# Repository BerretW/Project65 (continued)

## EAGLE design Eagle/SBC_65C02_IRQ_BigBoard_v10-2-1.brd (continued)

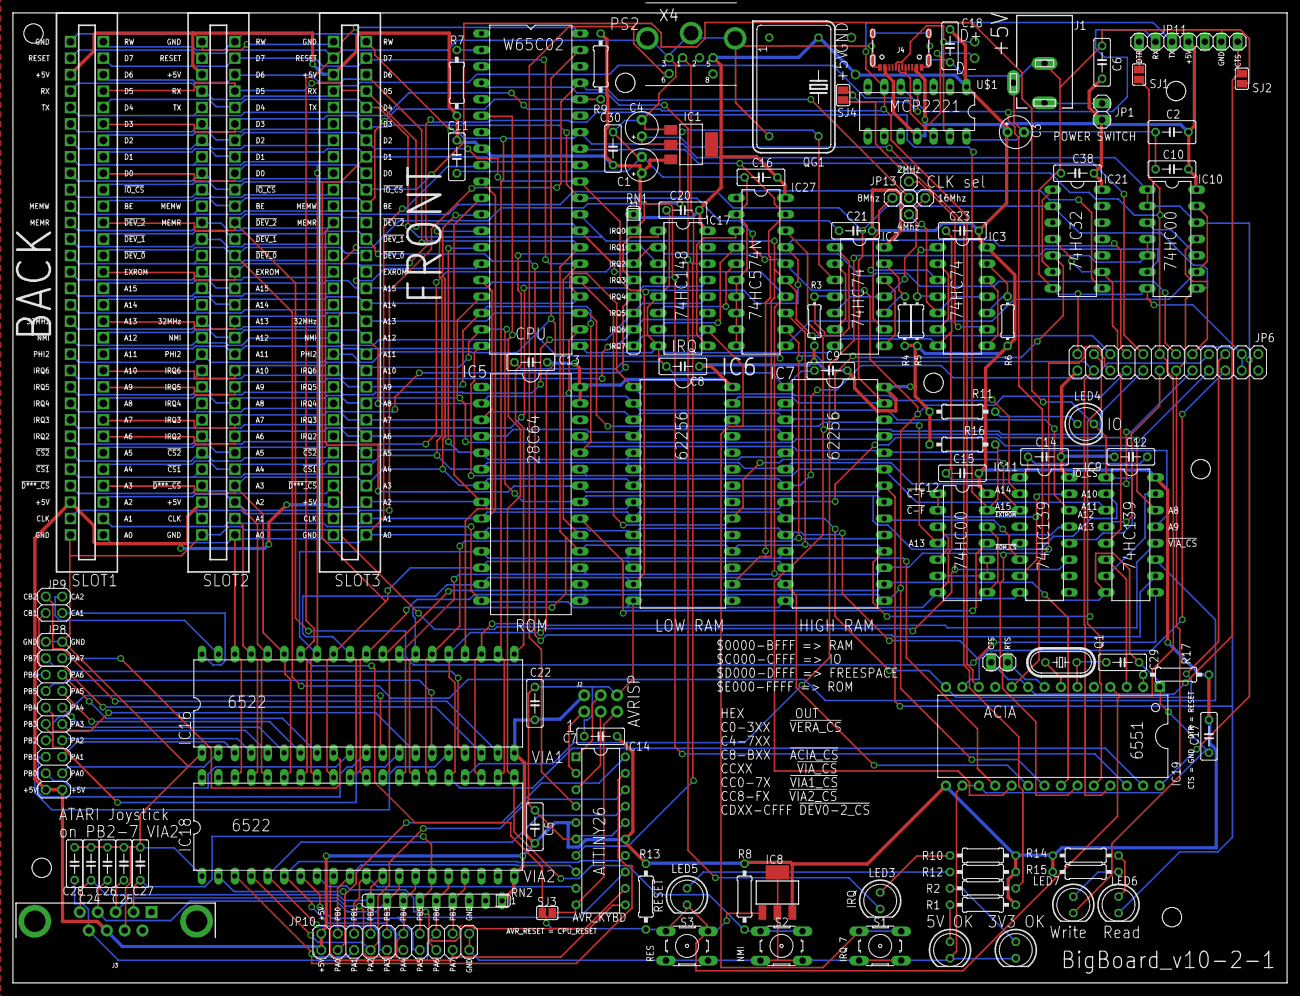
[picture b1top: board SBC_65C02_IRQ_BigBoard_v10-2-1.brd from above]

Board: 2 copper layers, 196.8 x 149.9 mm, 105 parts (0 on the bottom side), 155 nets.

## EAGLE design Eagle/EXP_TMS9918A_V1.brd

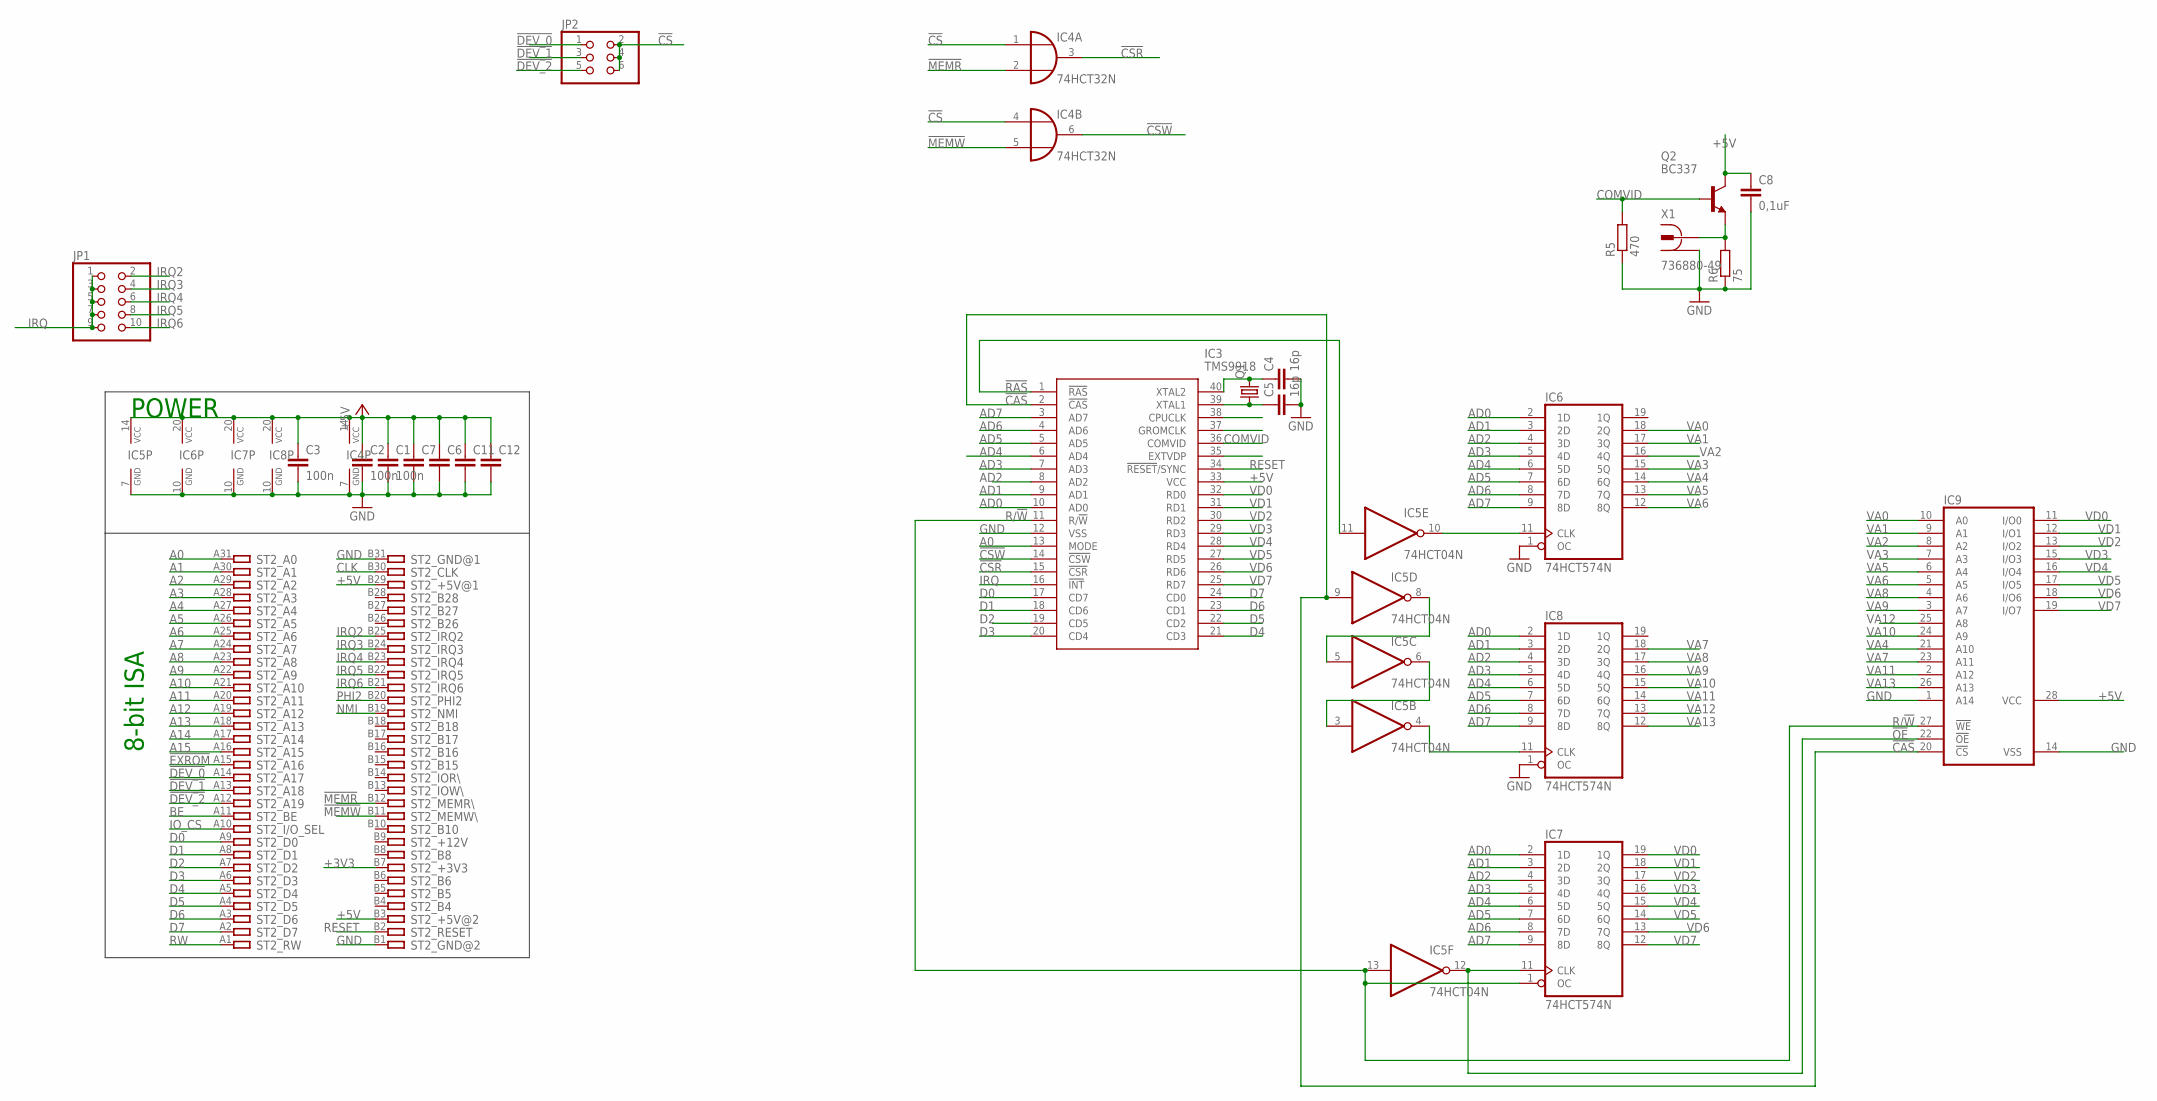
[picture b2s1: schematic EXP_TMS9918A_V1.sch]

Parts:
C1, C2, C3: 100n; C050-025X075
C4, C5: 16p; C050-024X044
C6, C7, C11, C12: C-EU050-035X075; C050-035X075
C8: 0,1uF; C050-024X044
IC3: TMS9918; DIP1524W53P254L5310H508Q40N
IC4: 74HCT32N; DIL14
IC5: 74HCT04N; DIL14
IC6, IC7, IC8: 74HCT574N; DIL20
IC9: 62256P; DIL28-6
JP1: PINHD-2X5; 2X05
JP2: PINHD-2X3; 2X03
Q1: CRYSTALHC49S; HC49/S
Q2: BC337; TO92
R5: 470; 0207/7
R6: 75; 0207/7
ST2: IBM8BIT_ISASHORT; APP_2X32_SHORT
X1: 736880-49

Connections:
!CAS: IC3.2 (!CAS), IC5.9 (I), IC9.20 (!CS)
!CS: IC4.1 (I0), IC4.4 (I0), JP2.2, JP2.4, JP2.6
!CSR: IC3.15 (!CSR), IC4.3 (O)
!CSW: IC3.14 (!CSW), IC4.6 (O)
!DEV_0: JP2.1, ST2.A14
!DEV_1: JP2.3, ST2.A13
!DEV_2: JP2.5, ST2.A12
!EXROM: ST2.A15
!MEMR: IC4.2 (I1), ST2.B12
!MEMW: IC4.5 (I1), ST2.B11
!OE: IC5.12 (O), IC7.11 (CLK), IC9.22 (!OE)
!RAS: IC3.1 (!RAS), IC5.11 (I)
+3V3: ST2.B7
+5V: C1.1, C2.1, C3.1, C6.1, C7.1, C8.1, C11.1, C12.1, IC3.33 (VCC), IC4.14 (VCC), IC5.14 (VCC), IC6.20 (VCC), IC7.20 (VCC), IC8.20 (VCC), IC9.28 (VCC), Q2.3 (C), ST2.B3, ST2.B29
A0: IC3.13 (MODE), ST2.A31
A1: ST2.A30
A2: ST2.A29
A3: ST2.A28
A4: ST2.A27
A5: ST2.A26
A6: ST2.A25
A7: ST2.A24
A8: ST2.A23
A9: ST2.A22
A10: ST2.A21
A11: ST2.A20
A12: ST2.A19
A13: ST2.A18
A14: ST2.A17
A15: ST2.A16
AD0: IC3.10 (AD0), IC6.2 (1D), IC7.2 (1D), IC8.2 (1D)
AD1: IC3.9 (AD1), IC6.3 (2D), IC7.3 (2D), IC8.3 (2D)
AD2: IC3.8 (AD2), IC6.4 (3D), IC7.4 (3D), IC8.4 (3D)
AD3: IC3.7 (AD3), IC6.5 (4D), IC7.5 (4D), IC8.5 (4D)
AD4: IC3.6 (AD4), IC6.6 (5D), IC7.6 (5D), IC8.6 (5D)
AD5: IC3.5 (AD5), IC6.7 (6D), IC7.7 (6D), IC8.7 (6D)
AD6: IC3.4 (AD6), IC6.8 (7D), IC7.8 (7D), IC8.8 (7D)
AD7: IC3.3 (AD7), IC6.9 (8D), IC7.9 (8D), IC8.9 (8D)
BE: ST2.A11
CLK: ST2.B30
COMVID: IC3.36 (COMVID), Q2.2 (B), R5.2
D0: IC3.17 (CD7), ST2.A9
D1: IC3.18 (CD6), ST2.A8
D2: IC3.19 (CD5), ST2.A7
D3: IC3.20 (CD4), ST2.A6
D4: IC3.21 (CD3), ST2.A5
D5: IC3.22 (CD2), ST2.A4
D6: IC3.23 (CD1), ST2.A3
D7: IC3.24 (CD0), ST2.A2
GND: C1.2, C2.2, C3.2, C4.2, C5.2, C6.2, C7.2, C8.2, C11.2, C12.2, IC3.12 (VSS), IC4.7 (GND), IC5.7 (GND), IC6.1 (OC), IC6.10 (GND), IC7.10 (GND), IC8.1 (OC), IC8.10 (GND), IC9.1 (A14), IC9.14 (VSS), R5.1, R6.1, ST2.B1, ST2.B31, X1.1, X1.1@1 (1), X1.1@2 (1)
IO_CS: ST2.A10
IRQ: IC3.16 (!INT), JP1.1, JP1.3, JP1.5, JP1.7, JP1.9
IRQ2: JP1.2, ST2.B25
IRQ3: JP1.4, ST2.B24
IRQ4: JP1.6, ST2.B23
IRQ5: JP1.8, ST2.B22
IRQ6: JP1.10, ST2.B21
unnamed: Q2.1 (E), R6.2, X1.2
unnamed: IC5.10 (O), IC6.11 (CLK)
unnamed: IC5.5 (I), IC5.8 (O)
unnamed: IC5.3 (I), IC5.6 (O)
unnamed: IC5.4 (O), IC8.11 (CLK)
unnamed: C4.1, IC3.40 (XTAL2), Q1.2
unnamed: C5.1, IC3.39 (XTAL1), Q1.1
NMI: ST2.B19
PHI2: ST2.B20
R/!W: IC3.11 (R/!W), IC5.13 (I), IC7.1 (OC), IC9.27 (!WE)
RESET: IC3.34 (!RESET!/SYNC), ST2.B2
RW: ST2.A1
VA0: IC6.18 (2Q), IC9.10 (A0)
VA1: IC6.17 (3Q), IC9.9 (A1)
VA2: IC6.16 (4Q), IC9.8 (A2)
VA3: IC6.15 (5Q), IC9.7 (A3)
VA4: IC6.14 (6Q), IC9.21 (A10)
VA5: IC6.13 (7Q), IC9.6 (A4)
VA6: IC6.12 (8Q), IC9.5 (A5)
VA7: IC8.18 (2Q), IC9.23 (A11)
VA8: IC8.17 (3Q), IC9.4 (A6)
VA9: IC8.16 (4Q), IC9.3 (A7)
VA10: IC8.15 (5Q), IC9.24 (A9)
VA11: IC8.14 (6Q), IC9.2 (A12)
VA12: IC8.13 (7Q), IC9.25 (A8)
VA13: IC8.12 (8Q), IC9.26 (A13)
VD0: IC3.32 (RD0), IC7.19 (1Q), IC9.11 (I/O0)
VD1: IC3.31 (RD1), IC7.18 (2Q), IC9.12 (I/O1)
VD2: IC3.30 (RD2), IC7.17 (3Q), IC9.13 (I/O2)
VD3: IC3.29 (RD3), IC7.16 (4Q), IC9.15 (I/O3)
VD4: IC3.28 (RD4), IC7.15 (5Q), IC9.16 (I/O4)
VD5: IC3.27 (RD5), IC7.14 (6Q), IC9.17 (I/O5)
VD6: IC3.26 (RD6), IC7.13 (7Q), IC9.18 (I/O6)
VD7: IC3.25 (RD7), IC7.12 (8Q), IC9.19 (I/O7)

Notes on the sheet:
POWER
8-bit ISA

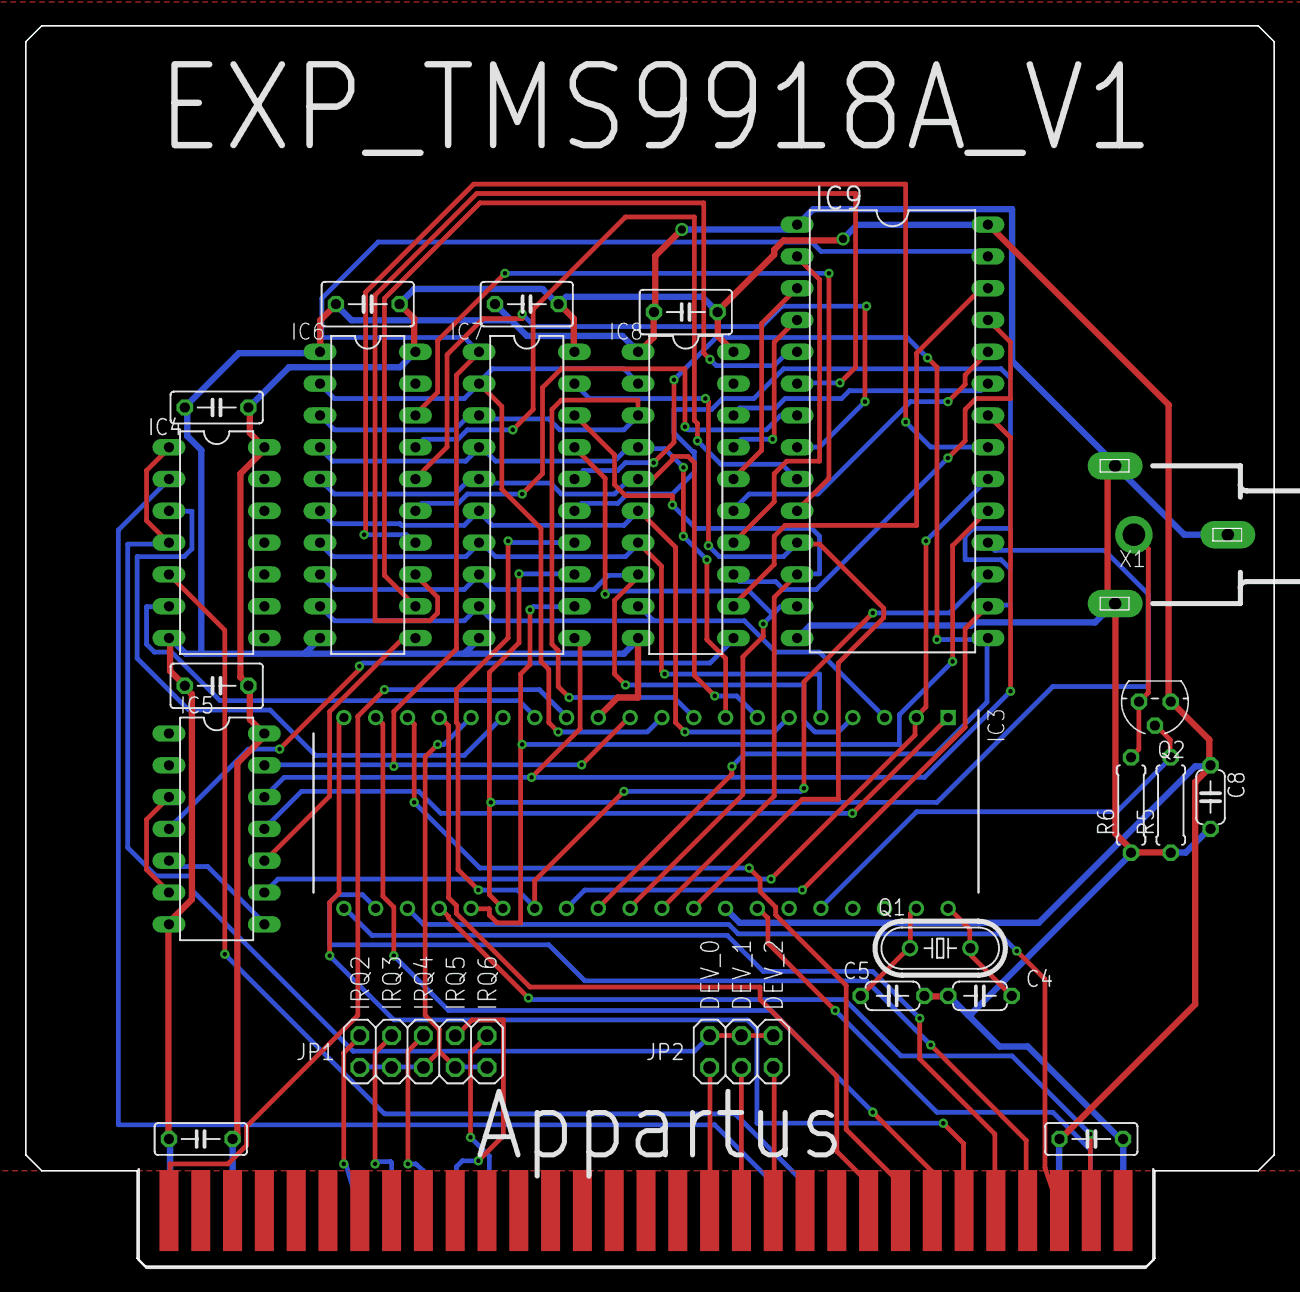
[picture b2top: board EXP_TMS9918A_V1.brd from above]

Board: 2 copper layers, 99.7 x 99.1 mm, 25 parts (0 on the bottom side), 68 nets.

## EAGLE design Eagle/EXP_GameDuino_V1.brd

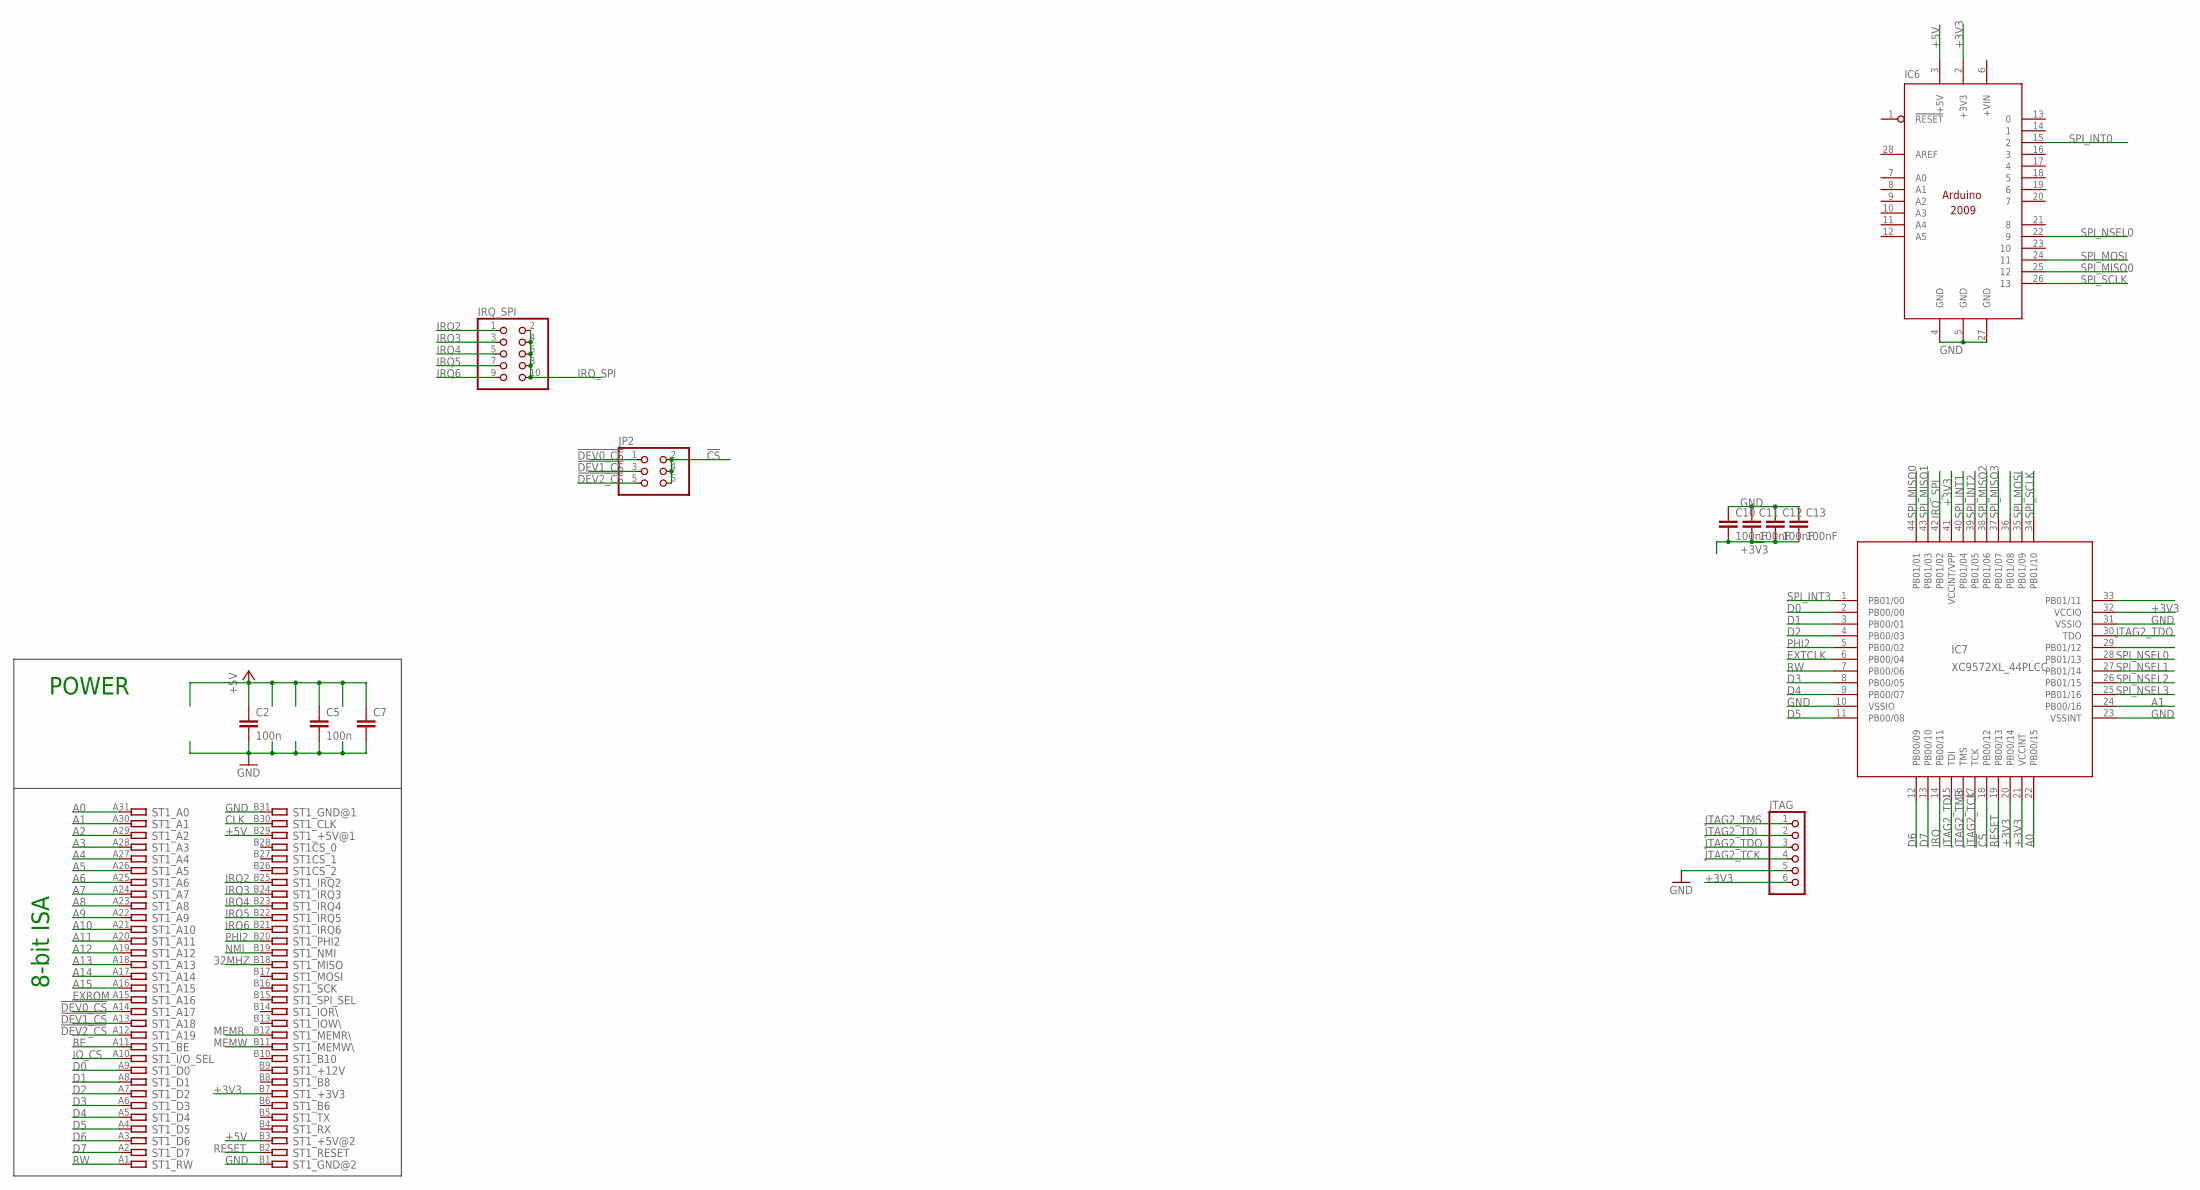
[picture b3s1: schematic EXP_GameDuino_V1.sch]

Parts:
C2, C5: 100n; C050-025X075
C7: C-EU050-035X075; C050-035X075
C10, C11, C12, C13: 100nF; C603
IC6: ARDUINO2009_10; ARDUINO2009
IC7: XC9572XL_44PLCC; S44
IRQ_SPI: PINHD-2X5; 2X05
JP2: PINHD-2X3; 2X03
JTAG: PINHD-1X6; 1X06
ST1: IBM8BIT_ISASHORT; APP_2X32_SHORT

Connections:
32MHZ: ST1.B18
!CS: IC7.18 (PB00/12), JP2.2, JP2.4, JP2.6
!DEV0_CS: JP2.1, ST1.A14
!DEV1_CS: JP2.3, ST1.A13
!DEV2_CS: JP2.5, ST1.A12
+3V3: C10.2, C11.2, C12.2, C13.2, IC6.2 (+3V3), IC7.20 (PB00/14), IC7.21 (VCCINT), IC7.32 (VCCIO), IC7.41 (VCCINT/VPP), JTAG.6, ST1.B7
+5V: C2.1, C5.1, C7.1, IC6.3 (+5V), ST1.B3, ST1.B29
A0: IC7.22 (PB00/15), ST1.A31
A1: IC7.24 (PB00/16), ST1.A30
A2: ST1.A29
A3: ST1.A28
A4: ST1.A27
A5: ST1.A26
A6: ST1.A25
A7: ST1.A24
A8: ST1.A23
A9: ST1.A22
A10: ST1.A21
A11: ST1.A20
A12: ST1.A19
A13: ST1.A18
A14: ST1.A17
A15: ST1.A16
BE: ST1.A11
CLK: ST1.B30
D0: IC7.2 (PB00/00), ST1.A9
D1: IC7.3 (PB00/01), ST1.A8
D2: IC7.4 (PB00/03), ST1.A7
D3: IC7.8 (PB00/05), ST1.A6
D4: IC7.9 (PB00/07), ST1.A5
D5: IC7.11 (PB00/08), ST1.A4
D6: IC7.12 (PB00/09), ST1.A3
D7: IC7.13 (PB00/10), ST1.A2
EXROM: ST1.A15
EXTCLK: IC7.6 (PB00/04)
GND: C2.2, C5.2, C7.2, C10.1, C11.1, C12.1, C13.1, IC6.4 (GND), IC6.5 (GND), IC6.27 (GND), IC7.10 (VSSIO), IC7.23 (VSSINT), IC7.31 (VSSIO), JTAG.5, ST1.B1, ST1.B31
IO_CS: ST1.A10
IRQ: IC7.14 (PB00/11)
IRQ2: IRQ_SPI.1, ST1.B25
IRQ3: IRQ_SPI.3, ST1.B24
IRQ4: IRQ_SPI.5, ST1.B23
IRQ5: IRQ_SPI.7, ST1.B22
IRQ6: IRQ_SPI.9, ST1.B21
IRQ_SPI: IC7.42 (PB01/02), IRQ_SPI.2, IRQ_SPI.4, IRQ_SPI.6, IRQ_SPI.8, IRQ_SPI.10
JTAG2_TCK: IC7.17 (TCK), JTAG.4
JTAG2_TDI: IC7.15 (TDI), JTAG.2
JTAG2_TDO: IC7.30 (TDO), JTAG.3
JTAG2_TMS: IC7.16 (TMS), JTAG.1
MEMR: ST1.B12
MEMW: ST1.B11
NMI: ST1.B19
PHI2: IC7.5 (PB00/02), ST1.B20
RESET: IC7.19 (PB00/13), ST1.B2
RW: IC7.7 (PB00/06), ST1.A1
SPI_INT0: IC6.15 (2)
SPI_INT1: IC7.40 (PB01/04)
SPI_INT2: IC7.39 (PB01/05)
SPI_INT3: IC7.1 (PB01/00)
SPI_MISO0: IC6.25 (12), IC7.44 (PB01/01)
SPI_MISO1: IC7.43 (PB01/03)
SPI_MISO2: IC7.38 (PB01/06)
SPI_MISO3: IC7.37 (PB01/07)
SPI_MOSI: IC6.24 (11), IC7.35 (PB01/09)
SPI_NSEL0: IC6.22 (9), IC7.28 (PB01/13)
SPI_NSEL1: IC7.27 (PB01/14)
SPI_NSEL2: IC7.26 (PB01/15)
SPI_NSEL3: IC7.25 (PB01/16)
SPI_SCLK: IC6.26 (13), IC7.34 (PB01/10)

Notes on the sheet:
POWER
8-bit ISA

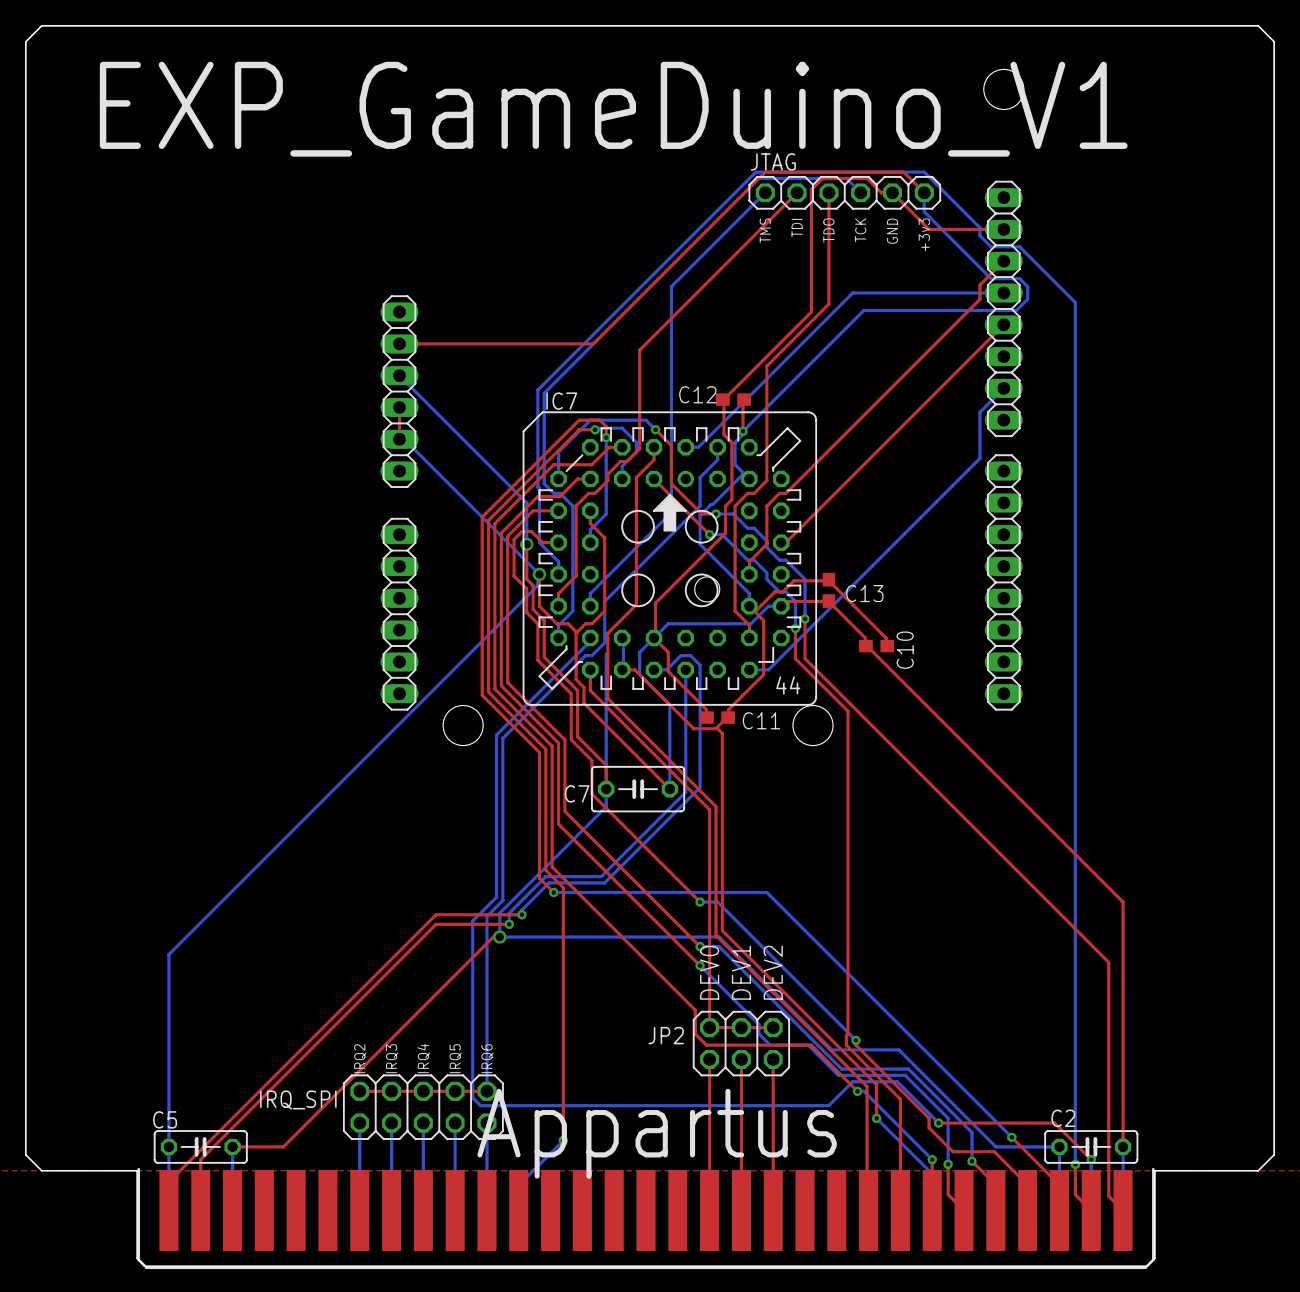
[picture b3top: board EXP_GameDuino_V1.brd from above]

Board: 2 copper layers, 99.7 x 99.1 mm, 13 parts (0 on the bottom side), 34 nets.

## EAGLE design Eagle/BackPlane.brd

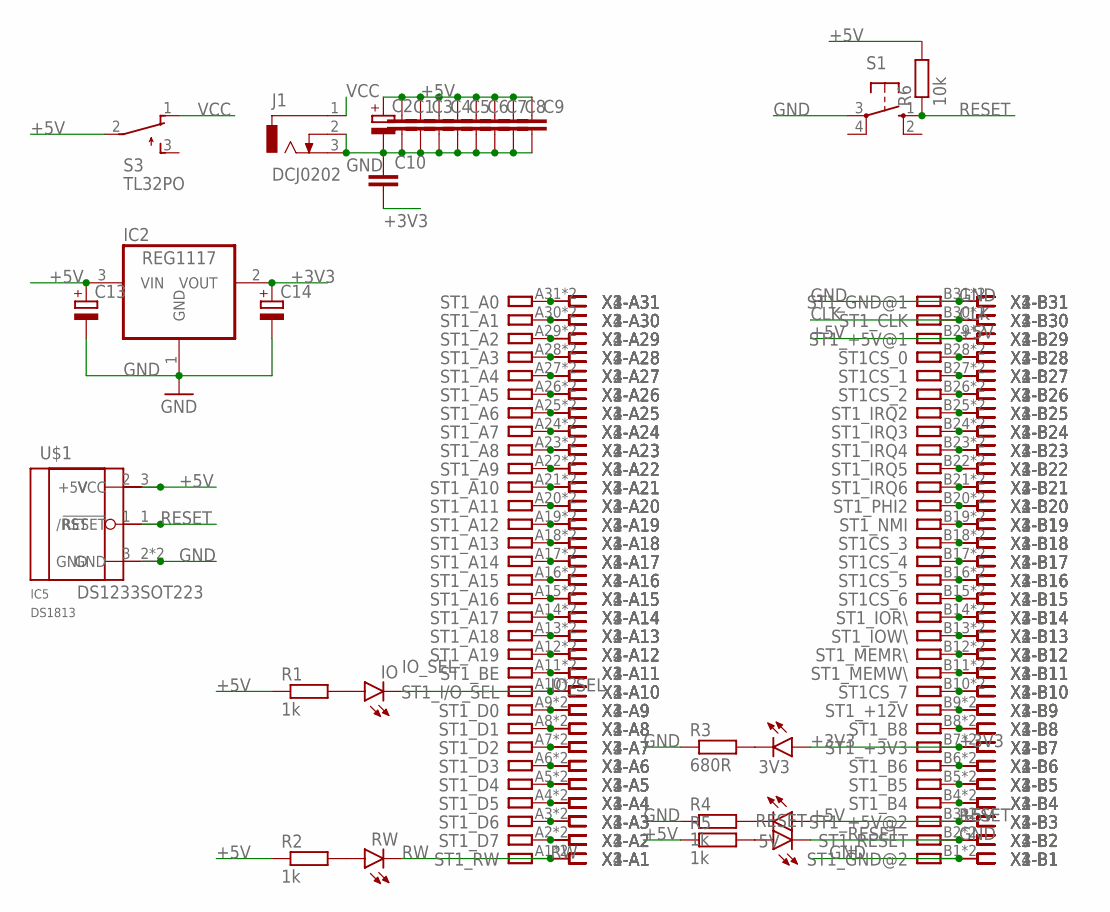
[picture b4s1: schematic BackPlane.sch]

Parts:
3V3, 5V: LED3MM
C1, C3, C4, C5, C6, C7, C8, C9: C-EU050-024X044; C050-024X044
C2: CPOL-EUE3.5-8; E3,5-8
C10: C-EU025-024X044; C025-024X044
C13, C14: CPOL-EUE2.5-5; E2,5-5
IC2: REG1117; SOT223
IC5: DS1813; TO-92
IO: LED3MM
J1: DCJ0202
R1, R2, R4, R5: 1k; 0207/7
R3: 680R; 0207/7
R6: 10k; 0207/7
RESET: LED3MM
RW: LED3MM
S1: 10-XX; B3F-10XX
S3: TL32PO; TL3XPO
ST1: IBM8BIT_ISA; APP_2X32_DOUBLE
U$1: DS1233SOT223; SOT223
X1, X2, X3, X4: ISA-SLOT; ISA-8

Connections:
+3V3: 3V3.A, C10.2, C14.+, IC2.2 (VOUT), ST1.B7, ST1.B38, X1.B7, X2.B7, X3.B7, X4.B7
+5V: 5V.A, C1.1, C2.+, C3.1, C4.1, C5.1, C6.1, C7.1, C8.1, C9.1, C13.+, IC2.3 (VIN), IC5.2 (+5V), R1.1, R2.1, R5.1, R6.2, S3.2, ST1.B3, ST1.B29, ST1.B34, ST1.B60, U$1.3 (VCC), X1.B3, X1.B29, X2.B3, X2.B29, X3.B3, X3.B29, X4.B3, X4.B29
CLK: ST1.B30, ST1.B61, X1.B30, X2.B30, X3.B30, X4.B30
GND: C1.2, C2.-, C3.2, C4.2, C5.2, C6.2, C7.2, C8.2, C9.2, C10.1, C13.-, C14.-, IC2.1 (GND), IC5.3 (GND), J1.2, J1.3, R3.1, R4.1, S1.3, ST1.B1, ST1.B31, ST1.B32, ST1.B62, U$1.2 (GND), U$1.4 (GND), X1.B1, X1.B31, X2.B1, X2.B31, X3.B1, X3.B31, X4.B1, X4.B31
IO_SEL: IO.K (C), ST1.A10, ST1.A41, X1.A10, X2.A10, X3.A10, X4.A10
unnamed: IO.A, R1.2
unnamed: ST1.A2, ST1.A33, X1.A2, X2.A2, X3.A2, X4.A2
unnamed: ST1.A3, ST1.A34, X1.A3, X2.A3, X3.A3, X4.A3
unnamed: ST1.A4, ST1.A35, X1.A4, X2.A4, X3.A4, X4.A4
unnamed: ST1.A5, ST1.A36, X1.A5, X2.A5, X3.A5, X4.A5
unnamed: ST1.A6, ST1.A37, X1.A6, X2.A6, X3.A6, X4.A6
unnamed: ST1.A7, ST1.A38, X1.A7, X2.A7, X3.A7, X4.A7
unnamed: ST1.A8, ST1.A39, X1.A8, X2.A8, X3.A8, X4.A8
unnamed: ST1.A9, ST1.A40, X1.A9, X2.A9, X3.A9, X4.A9
unnamed: R2.2, RW.A
unnamed: ST1.A11, ST1.A42, X1.A11, X2.A11, X3.A11, X4.A11
unnamed: ST1.A12, ST1.A43, X1.A12, X2.A12, X3.A12, X4.A12
unnamed: ST1.A13, ST1.A44, X1.A13, X2.A13, X3.A13, X4.A13
unnamed: ST1.A14, ST1.A45, X1.A14, X2.A14, X3.A14, X4.A14
unnamed: ST1.A15, ST1.A46, X1.A15, X2.A15, X3.A15, X4.A15
unnamed: ST1.A16, ST1.A47, X1.A16, X2.A16, X3.A16, X4.A16
unnamed: ST1.A17, ST1.A48, X1.A17, X2.A17, X3.A17, X4.A17
unnamed: ST1.A18, ST1.A49, X1.A18, X2.A18, X3.A18, X4.A18
unnamed: ST1.A19, ST1.A50, X1.A19, X2.A19, X3.A19, X4.A19
unnamed: ST1.A20, ST1.A51, X1.A20, X2.A20, X3.A20, X4.A20
unnamed: ST1.A21, ST1.A52, X1.A21, X2.A21, X3.A21, X4.A21
unnamed: ST1.A22, ST1.A53, X1.A22, X2.A22, X3.A22, X4.A22
unnamed: ST1.A23, ST1.A54, X1.A23, X2.A23, X3.A23, X4.A23
unnamed: ST1.A24, ST1.A55, X1.A24, X2.A24, X3.A24, X4.A24
unnamed: ST1.A25, ST1.A56, X1.A25, X2.A25, X3.A25, X4.A25
unnamed: ST1.A26, ST1.A57, X1.A26, X2.A26, X3.A26, X4.A26
unnamed: ST1.A27, ST1.A58, X1.A27, X2.A27, X3.A27, X4.A27
unnamed: ST1.A28, ST1.A59, X1.A28, X2.A28, X3.A28, X4.A28
unnamed: ST1.A29, ST1.A60, X1.A29, X2.A29, X3.A29, X4.A29
unnamed: ST1.A30, ST1.A61, X1.A30, X2.A30, X3.A30, X4.A30
unnamed: ST1.A31, ST1.A62, X1.A31, X2.A31, X3.A31, X4.A31
unnamed: ST1.B4, ST1.B35, X1.B4, X2.B4, X3.B4, X4.B4
unnamed: ST1.B5, ST1.B36, X1.B5, X2.B5, X3.B5, X4.B5
unnamed: ST1.B6, ST1.B37, X1.B6, X2.B6, X3.B6, X4.B6
unnamed: ST1.B8, ST1.B39, X1.B8, X2.B8, X3.B8, X4.B8
unnamed: ST1.B9, ST1.B40, X1.B9, X2.B9, X3.B9, X4.B9
unnamed: ST1.B10, ST1.B41, X1.B10, X2.B10, X3.B10, X4.B10
unnamed: ST1.B11, ST1.B42, X1.B11, X2.B11, X3.B11, X4.B11
unnamed: ST1.B12, ST1.B43, X1.B12, X2.B12, X3.B12, X4.B12
unnamed: ST1.B13, ST1.B44, X1.B13, X2.B13, X3.B13, X4.B13
unnamed: ST1.B14, ST1.B45, X1.B14, X2.B14, X3.B14, X4.B14
unnamed: ST1.B15, ST1.B46, X1.B15, X2.B15, X3.B15, X4.B15
unnamed: ST1.B16, ST1.B47, X1.B16, X2.B16, X3.B16, X4.B16
unnamed: ST1.B17, ST1.B48, X1.B17, X2.B17, X3.B17, X4.B17
unnamed: ST1.B18, ST1.B49, X1.B18, X2.B18, X3.B18, X4.B18
unnamed: ST1.B19, ST1.B50, X1.B19, X2.B19, X3.B19, X4.B19
unnamed: ST1.B20, ST1.B51, X1.B20, X2.B20, X3.B20, X4.B20
unnamed: ST1.B21, ST1.B52, X1.B21, X2.B21, X3.B21, X4.B21
unnamed: ST1.B22, ST1.B53, X1.B22, X2.B22, X3.B22, X4.B22
unnamed: ST1.B23, ST1.B54, X1.B23, X2.B23, X3.B23, X4.B23
unnamed: ST1.B24, ST1.B55, X1.B24, X2.B24, X3.B24, X4.B24
unnamed: ST1.B25, ST1.B56, X1.B25, X2.B25, X3.B25, X4.B25
unnamed: ST1.B26, ST1.B57, X1.B26, X2.B26, X3.B26, X4.B26
unnamed: ST1.B27, ST1.B58, X1.B27, X2.B27, X3.B27, X4.B27
unnamed: ST1.B28, ST1.B59, X1.B28, X2.B28, X3.B28, X4.B28
unnamed: 3V3.K (C), R3.2
unnamed: 5V.K (C), R4.2
unnamed: R5.2, RESET.A
RESET: IC5.1 (/RST), R6.1, RESET.K (C), S1.1 (S), ST1.B2, ST1.B33, U$1.1 (!RESET), X1.B2, X2.B2, X3.B2, X4.B2
RW: RW.K (C), ST1.A1, ST1.A32, X1.A1, X2.A1, X3.A1, X4.A1
VCC: J1.1, S3.1 (O)

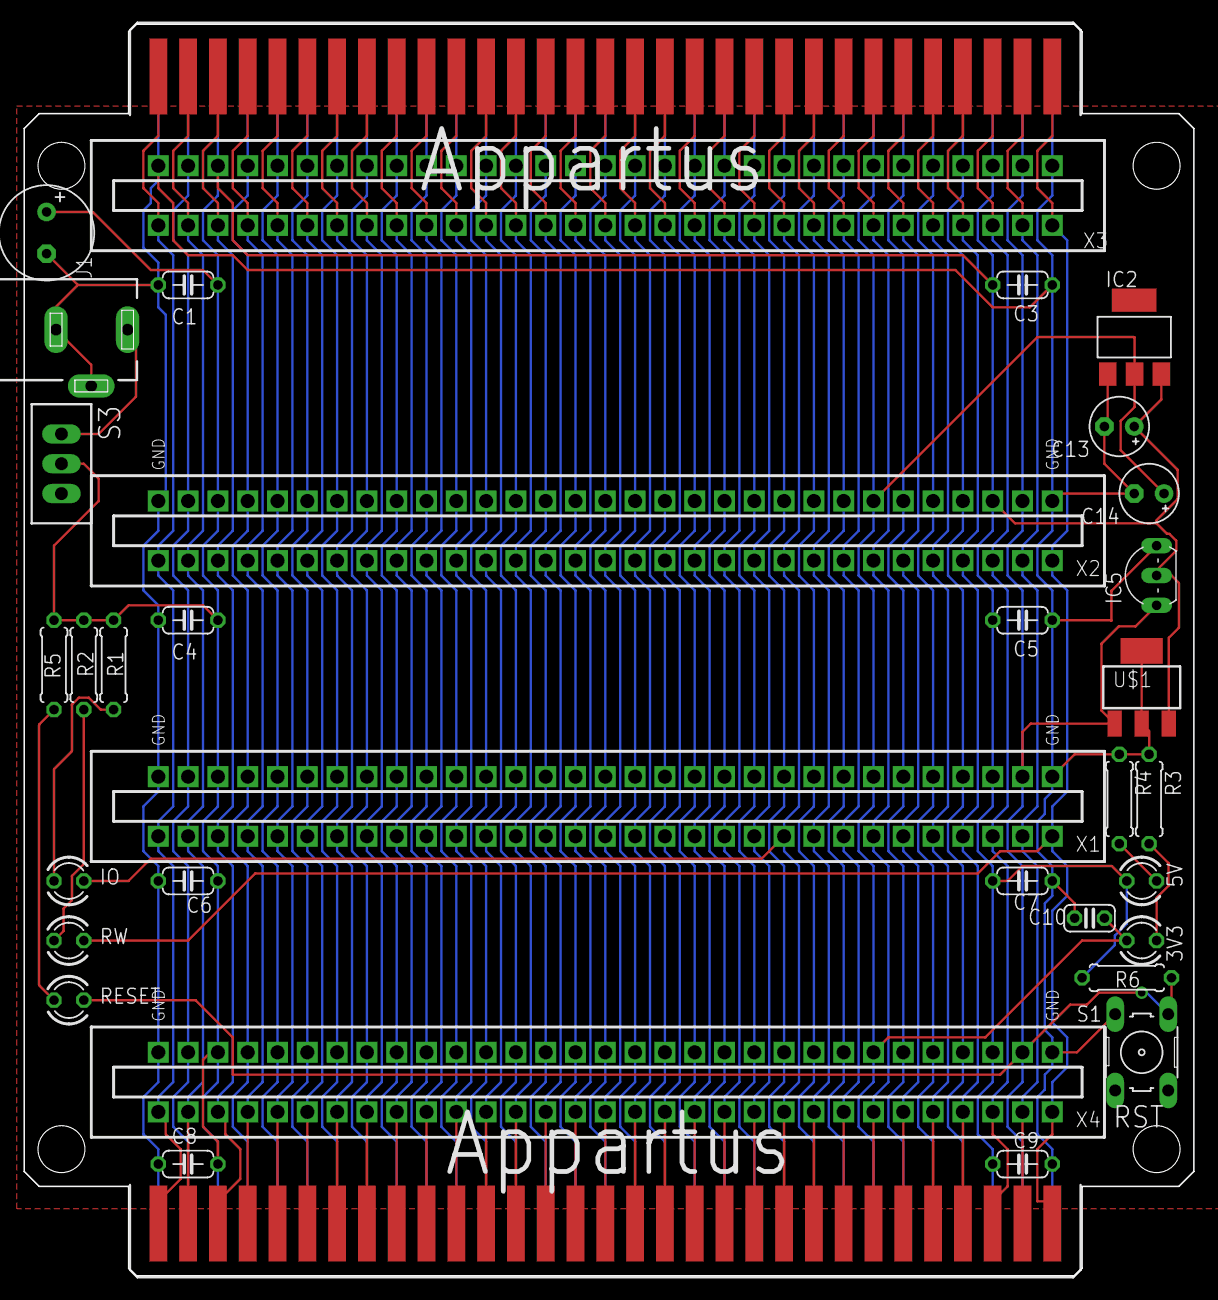
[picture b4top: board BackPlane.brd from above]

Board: 2 copper layers, 99.7 x 106.7 mm, 34 parts (0 on the bottom side), 66 nets.

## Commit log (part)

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2020-10-21 Init
2021-01-10 + Photos
2021-12-22 New version
    9-1-3
2026-04-13 Přidání minimalního bootloaderu a souvisejících skriptů pro kompilaci
2026-04-13 Add component list for SBC 65C02 IRQ BigBoard v10-2-1
2026-04-13 Oprava NMI a IRQ ISR pro správné generování signálů z VIA1
2026-04-13 Add Intel HEX loader and RAM test functionality
    - Updated build_minimal.bat to include ihex.asm in the build process.
    - Modified jumptable.asm to adjust reset and interrupt vectors.
    - Enhanced main_min.c to support loading Intel HEX files and added corresponding user prompts.
    - Implemented ihex.asm for parsing and loading Intel HEX format data into RAM.
    - Created ramtest.asm for testing RAM functionality with various patterns and address checks.
    - Added bin2hex.py script to convert binary output to Intel HEX format.
2026-04-13 Refactor code structure for improved readability and maintainability
2026-04-13 Přidání ACIA inicializace a zpoždění do RAM testu; vytvoření skokové tabulky pro ROM rutiny
2026-04-13 Přidání kontroly prázdných bloků do konverze binárního souboru na Intel HEX
2026-04-16 Implement core emulator components: IRQ latch, RAM, ROM, and VIA
    - Added `irq_latch.rs` to manage IRQ priority and acknowledge mechanisms.
    - Introduced `ram.rs` for generic RAM handling with read/write capabilities.
    - Created `rom.rs` to handle 8 KB read-only memory with binary loading.
    - Developed `via.rs` for W65C22 VIA emulation, including timer and interrupt management.
    - Established `main.rs` as the entry point for the emulator, integrating components and TCP serial communication.
2026-04-16 Přidání podpory pro TCP připojení do P65 uploaderu; refaktoring kódu pro zjednodušení správy sériového a TCP připojení
2026-04-16 Refactor ACIA and VIA structures for public access; enhance Bus with chip family and timing analysis
    - Made internal fields of Acia and Via structs public for easier access.
    - Introduced ChipFamily enum to represent different address decoder families and their propagation delays.
    - Added timing analysis methods to the Bus struct to evaluate address decode delays based on the chip family.
    - Updated Bus initialization to set the chip family from command line arguments.
    - Enhanced the App struct to include a right panel for displaying CPU, VIA, ACIA, and IRQ information.
    - Implemented new modal dialogs for editing memory and CPU registers with keyboard handling.
2026-04-16 Add chiptest configuration and jump table, implement SAA1099 and TMS9918A emulation
    - Created `chiptest.cfg` for linker configuration of the chip test program.
    - Added `jumptable.inc65` for ROM jump table addresses to facilitate calling ROM routines.
    - Implemented `Saa1099` sound generator emulation in `saa1099.rs`, including bus interface and register handling.
    - Developed `Tms9918a` video display processor emulation in `tms9918a.rs`, covering bus interface, rendering, and IRQ handling.
2026-04-16 Add VDP text output functionality and update chiptest.asm
    - Included vdp_text.inc65 for TMS9918A text output handling.
    - Modified chiptest.asm to initialize VDP, display test results, and manage text output.
    - Added string definitions for titles and test results in chiptest.asm.
    - Enhanced the display logic for test results (OK/FAIL) on the VDP screen.
2026-04-16 Add RAMDisk filesystem and interactive shell to AppartusOS
    - Implemented `appartus_ramdisk.asm` for RAMDisk functionality including initialization, file management, and memory operations.
    - Created `appartus_shell.asm` to provide an interactive shell with commands for file operations, memory management, and system control.
    - Introduced `appartus_zp.asm` for zero page allocations to optimize memory usage for OS operations.
    - Enhanced command handling in the shell for loading, saving, deleting, and running files from the RAMDisk.
    - Added string handling and parsing utilities for command input processing.
2026-04-16 Implement VFS layer with file-descriptor API; add file I/O commands to AppartusOS shell
2026-04-17 Optimize BASIC interpreter flow and fix stack handling in line storage
2026-04-17 Preserve byte counter during hex gathering in _cmd_hexd
2026-04-17 Update README.md to enhance hardware overview and features section
2026-04-17 Add new schematic for SBC 65C02 IRQ BigBoard v10-2-1
2026-04-17 Implement LSAVE command in AppartusOS to save Intel HEX data to RAMDisk, including address range tracking and checksum verification. Refactor existing HEXD command code for clarity and efficiency.
2026-04-17 Odstranění nepotřebných souborů a přidání nového příkazu pro grep do nastavení
2026-04-17 Přidání nových příkazů pro spuštění build_appartus.bat a oprava 16-bitového dekrementu v _bas_store_line
2026-04-17 Přidání podpory pro hexadecimální literály v příkazu _bas_parse_num a implementace nové funkce _bas_parse_hex pro jejich zpracování
2026-04-18 Aktualizace verze P65 BASIC na v1.1 a AppartusOS na v1.2. Přidání funkce LSAVE pro příjem HEX souborů a uložení do RAMDisku. Přidání ukázkového programu hello.asm a jeho HEX souboru.
2026-04-18 Oprava inicializace NMI v utils.asm pro správnou konfiguraci VIA1 a úprava ovladače PS/2 klávesnice v pckybd.asm pro čtení z VIA1. Aktualizace README.md s informacemi o opravách.
2026-04-18 Add memory monitor and VERA detection test tools
    - Implemented `mem_mon.asm`, a memory monitor inspired by MS-DOS DEBUG, allowing memory dumping and writing.
    - Added `vera_test.asm` to test the presence of the VERA chip in the system, verifying register read/write functionality.
    - Generated binary, hex, and object files for both tools.
    - Included assembly instructions for building and using the tools in AppartusOS.
2026-04-18 Optimalizace čtení bajtů v dump_row a úprava get_line pro blokující ACIA příjem
2026-04-22 Add new tools for FPGA flashing and VDP font definition
    - Introduced `espi_update_fpga.py` for SPI command handling and flash programming.
    - Added `build.bat` for building the Vera test project.
    - Included `font.h` containing the VDP character set definitions for the BBC-128 homebrew computer.
    - Updated `vera_test.o` binary file to reflect changes.
2026-04-22 Add preliminary documentation for VERA Programmer's Reference
    This commit introduces the VERA Programmer's Reference document, detailing the architecture and functionality of the Versatile Embedded Retro Adapter (VERA). The documentation includes information on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
2026-04-22 Přidání nových skriptů pro testování VERA a aktualizace souvisejících souborů
2026-04-22 Add preliminary documentation for VERA Programmer's Reference
    - Introduced a new markdown file `Firmware/vera.md` detailing the VERSatile Embedded Retro Adapter (VERA).
    - Documented features including video generation, sound capabilities, SPI controller, and memory layout.
    - Included comprehensive descriptions of registers, VRAM access, display composer, layer configurations, sprite attributes, and audio functionalities.
    - Added tables for register definitions, VRAM address space layout, and audio data formats.
    - Emphasized initialization requirements and provided examples for usage.
2026-04-23 Přidání registrů pro ovládání VERA a úprava inicializace video režimu
2026-04-23 Přidání nových registrů pro ovládání VERA a úprava barevného schématu textového režimu
2026-04-27 Update .gitignore to include .claude directory
2026-04-27 asda
2026-05-05 Add new media files: V9-1.jpg, V6_Gamduino_Demo.mp4, and V6_Terminal_WozMon.mp4
